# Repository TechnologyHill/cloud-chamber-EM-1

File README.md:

# Cloud Chamber EM-1

[more about cloud chamber](https://en.wikipedia.org/wiki/Cloud_chamber)

#### Our goal is make a small cloud chamber based on thermoelectric cooling.
#### viewport size is 100 mm x 200 mm.

")
")

## Cooling system

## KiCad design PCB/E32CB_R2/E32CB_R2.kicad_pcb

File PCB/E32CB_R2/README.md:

# ESP32 Control Board
**E32CB_R2**

KiCad render of PCB

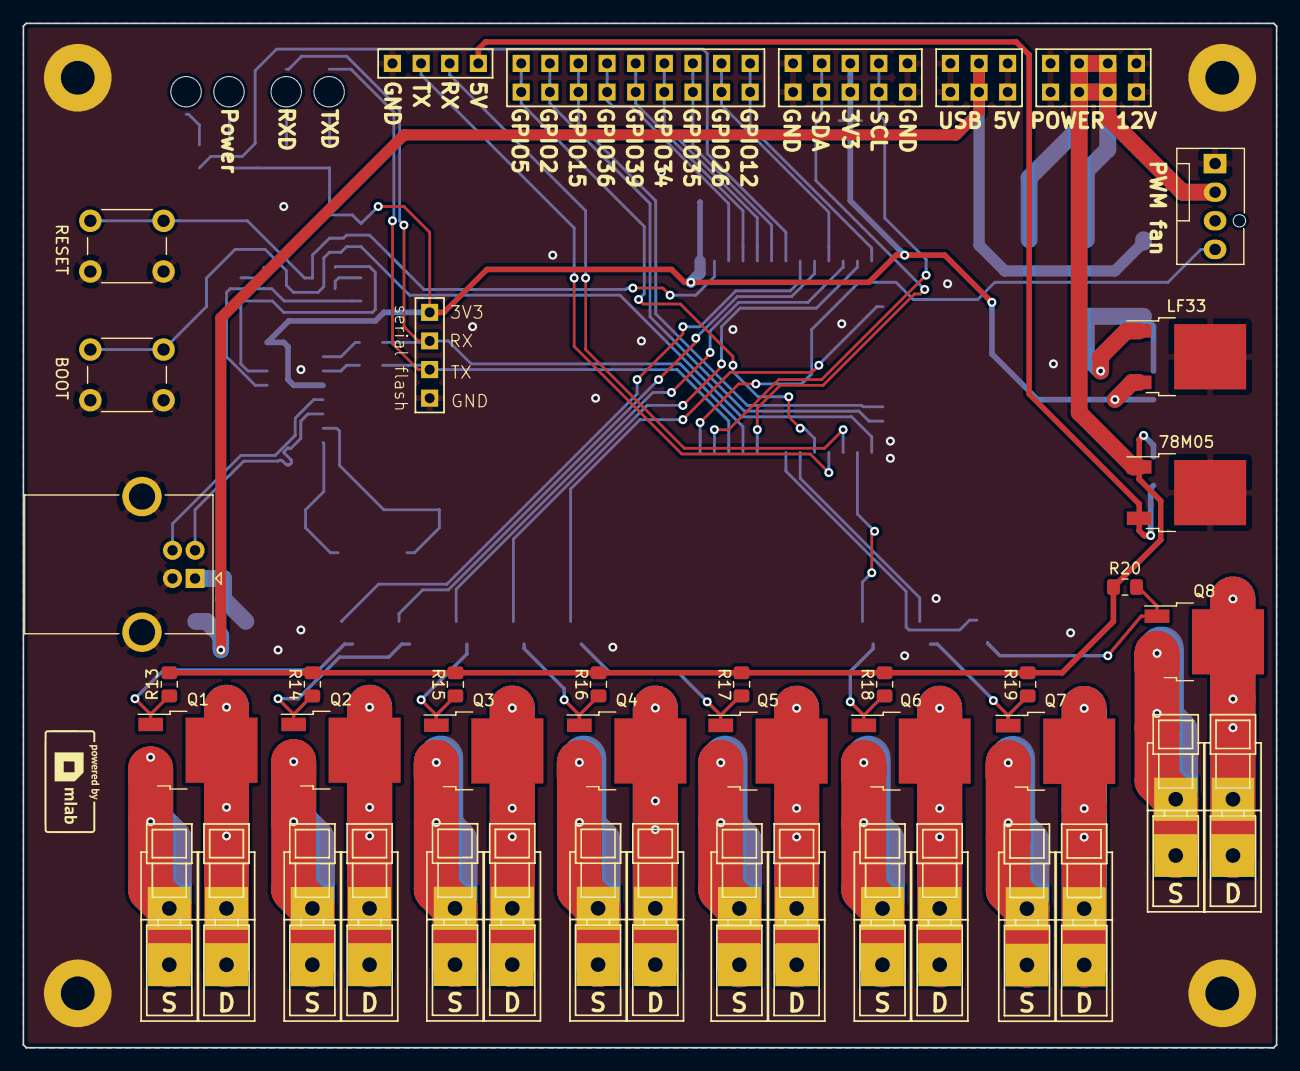
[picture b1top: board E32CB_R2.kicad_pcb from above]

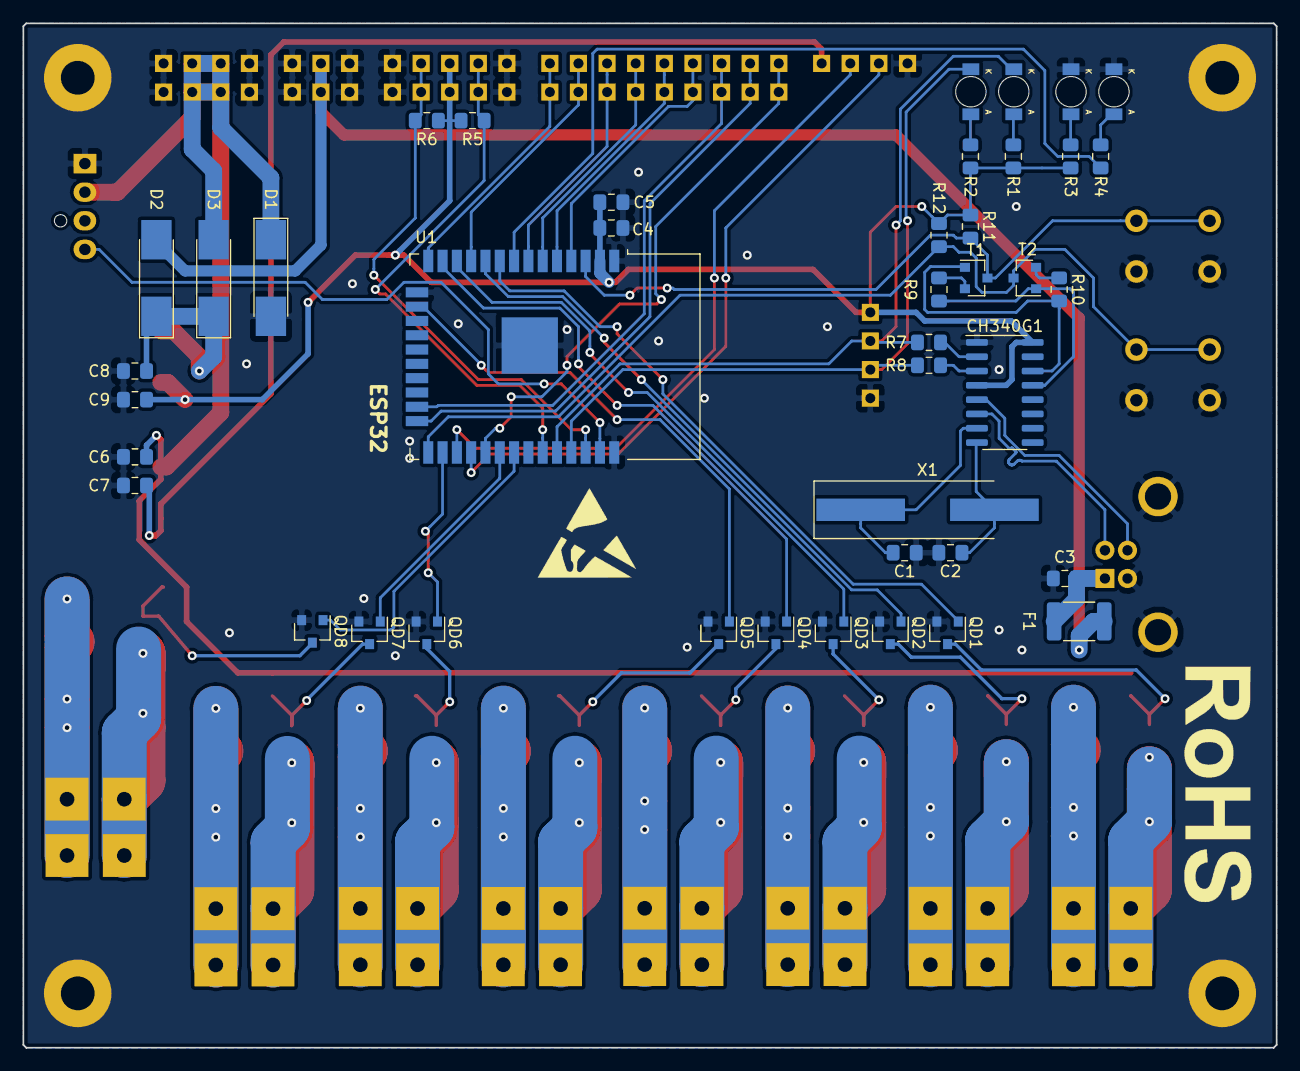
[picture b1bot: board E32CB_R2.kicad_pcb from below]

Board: 2 copper layers, 111.3 x 90.9 mm, 90 parts (42 on the bottom side), 72 nets.

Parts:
78M05: L7805; TO-252-2
BOOT: FLASH; SW_PUSH_6mm
C1, C2: 22p; C_0805_2012Metric_Pad1.15x1.40mm_HandSolder
C3: 10nF; C_0805_2012Metric_Pad1.15x1.40mm_HandSolder
C4, C7, C8: 100nF; C_0805_2012Metric_Pad1.15x1.40mm_HandSolder
C5: 10uF; C_0805_2012Metric_Pad1.15x1.40mm_HandSolder
C6: 330nF; C_0805_2012Metric_Pad1.15x1.40mm_HandSolder
C9: 2.2uF; C_0805_2012Metric_Pad1.15x1.40mm_HandSolder
CH340G1: CH340G; SOIC-16_3.9x9.9mm_P1.27mm
D: D; WAGO256
D1, D2, D3: 1N4007; D_MELF_Handsoldering
D#2, D#3, D#4, D#5, D#6, D#7, D#8: D; WAGO256
F1: 1A; Fuse_1812_4532Metric_Pad1.30x3.40mm_HandSolder
H1, H2, H3, H4: M3; MountingHole_3mm
J1: GPIO_HEADER; Straight_2x09
J2: Power; Straight_2x04
J3: USB_B; USB_B_OST_USB-B1HSxx_Horizontal
J4: USB +5V; Straight_2x03
J5: NEXTION; Straight_1x04
J6: I2C; Straight_2x05
J23: serial flash; Straight_1x04
LED1: RXD; LED_1206
LED2: TXD; LED_1206
LED3: Power; LED_1206
LED4: Signal; LED_1206
LF33: LF33_TO252; TO-252-2
PWM fan: Conn_01x04; FanPinHeader_1x04_P2.54mm_Vertical
Q1, Q2, Q3, Q4, Q5, Q6, Q7, Q8: IRLR8743; TO-252-2
QD1, QD2, QD3, QD4, QD5, QD6, QD7, QD8: BSS138; SOT-23
R1, R2, R3, R4: 1k; R_0805_2012Metric_Pad1.15x1.40mm_HandSolder
R5, R6: 1k2; R_0805_2012Metric_Pad1.15x1.40mm_HandSolder
R7, R8, R13, R14, R15, R16, R17, R18, R19, R20: 470R; R_0805_2012Metric_Pad1.15x1.40mm_HandSolder
R9, R10: 12k; R_0805_2012Metric_Pad1.15x1.40mm_HandSolder
R11, R12: 10k; R_0805_2012Metric_Pad1.15x1.40mm_HandSolder
RESET: RESET; SW_PUSH_6mm
S: S; WAGO256
S#2, S#3, S#4, S#5, S#6, S#7, S#8: S; WAGO256
T1, T2: S8050; SOT-23
U1: ESP32-WROOM-32
X1: 12MHz; Crystal_SMD_HC49-SD_HandSoldering

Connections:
+3V3: C4.1, C5.1, C9.1, CH340G1.4, CH340G1.16, J6.5, J6.6, J23.1, LF33.3, R1.2, R2.2, R3.2, R5.1, R6.1, R11.1, R12.1, U1.2
+5V: D2.2, F1.1, J4.3, J4.4
+12V: 78M05.1, C6.1, D1.1, D3.2, J2.3, J2.4, J2.5, J2.6, PWM fan.2, R13.1, R14.1, R15.1, R16.1, R17.1, R18.1, R19.1, R20.1
/EN: R11.2, RESET.1, T1.3, U1.3
/I2C_SCL: J6.7, J6.8, R6.2, U1.36
/I2C_SDA: J6.3, J6.4, R5.2, U1.33
/IO_0: BOOT.1, R12.2, T2.3, U1.25
/Q1: QD1.1, U1.9
/Q2: QD2.1, U1.10
/Q3: QD3.1, U1.12
/Q4: QD4.1, U1.13
/Q5: QD5.1, U1.16
/Q6: QD6.1, U1.26
/Q7: QD7.1, U1.30
/Q8: QD8.1, U1.31
/RXD: J23.2, LED1.1, R7.1, U1.34
/TXD: J23.3, LED2.1, R8.1, U1.35
/U2_RXD: J5.3, U1.27
/U2_TXD: J5.2, U1.28
/USB_N: CH340G1.6, J3.2
/USB_P: CH340G1.5, J3.3
/display_Vin: 78M05.3, C7.1, J5.4
/fan1: PWM fan.4, U1.37
/gpi34: J1.11, J1.12, U1.6
/gpi35: J1.13, J1.14, U1.7
/gpi36: J1.7, J1.8, U1.4
/gpi39: J1.9, J1.10, U1.5
/gpio2: J1.3, J1.4, U1.24
/gpio5: J1.1, J1.2, U1.29
/gpio12: J1.17, J1.18, U1.14
/gpio15: J1.5, J1.6, U1.23
/gpio26: J1.15, J1.16, U1.11
/s_LED: R4.2, U1.8
GND: 78M05.2, BOOT.2, C1.2, C2.2, C3.2, C4.2, C5.2, C6.2, C7.2, C8.2, C9.2, CH340G1.1, D1.2, H1.1, H2.1, H3.1, H4.1, J2.1, J2.2, J2.7, J2.8, J3.4, J3.5, J4.1, J4.2, J4.5, J4.6, J5.1, J6.1, J6.2, J6.9, J6.10, J23.4, LED3.1, LED4.1, LF33.2, PWM fan.1, QD1.2, QD2.2, QD3.2, QD4.2, QD5.2, QD6.2, QD7.2, QD8.2, RESET.2, U1.1, U1.15, U1.38, U1.39
unnamed: C8.1, D2.1, D3.1, LF33.1
unnamed: C1.1, CH340G1.7, X1.1
unnamed: C2.1, CH340G1.8, X1.2
unnamed: C3.1, F1.2, J3.1
unnamed: CH340G1.2, R7.2
unnamed: CH340G1.3, R8.2
unnamed: CH340G1.13, R9.2, T2.1
unnamed: CH340G1.14, R10.2, T1.1
unnamed: D#7.1, Q1.2
unnamed: Q1.3, S#7.1
unnamed: D#8.1, Q2.2
unnamed: Q2.3, S#8.1
unnamed: D.1, Q3.2
unnamed: Q3.3, S#2.1
unnamed: D#2.1, Q4.2
unnamed: Q4.3, S.1
unnamed: D#6.1, Q7.2
unnamed: Q7.3, S#3.1
unnamed: D#3.1, Q8.2
unnamed: Q8.3, S#4.1
unnamed: D#4.1, Q5.2
unnamed: Q5.3, S#6.1
unnamed: D#5.1, Q6.2
unnamed: Q6.3, S#5.1
unnamed: LED1.2, R1.1
unnamed: LED2.2, R2.1
unnamed: LED3.2, R3.1
unnamed: LED4.2, R4.1
unnamed: Q1.1, QD1.3, R13.2
unnamed: Q2.1, QD2.3, R14.2
unnamed: Q3.1, QD3.3, R15.2
unnamed: Q4.1, QD4.3, R16.2
unnamed: Q5.1, QD5.3, R17.2
unnamed: Q6.1, QD6.3, R18.2
unnamed: Q7.1, QD7.3, R19.2
unnamed: Q8.1, QD8.3, R20.2
unnamed: R9.1, T1.2
unnamed: R10.1, T2.2

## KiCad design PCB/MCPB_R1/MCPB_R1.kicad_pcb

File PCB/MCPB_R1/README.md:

# MCP9808 Board
**MCPB_R1**

top view of PCB

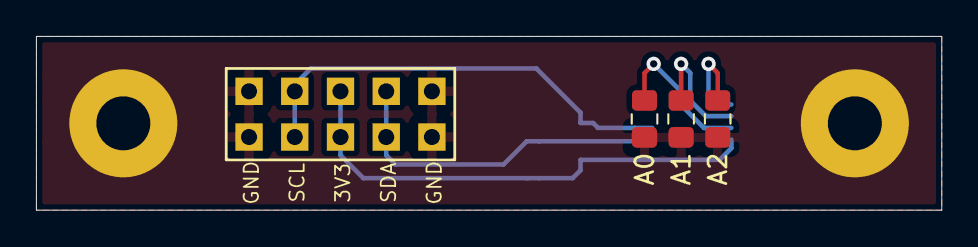
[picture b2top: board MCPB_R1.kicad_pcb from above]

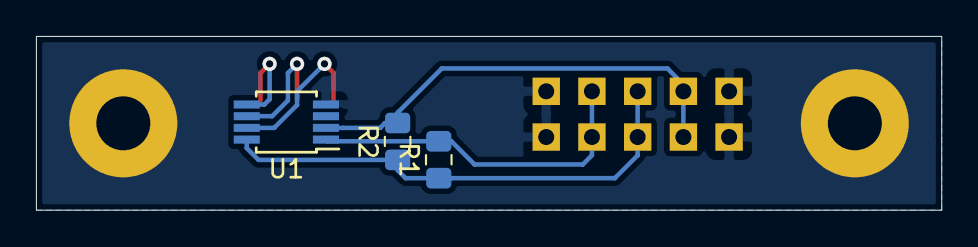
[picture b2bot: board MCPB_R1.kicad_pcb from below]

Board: 2 copper layers, 50.3 x 9.7 mm, 9 parts (3 on the bottom side), 7 nets.

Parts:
A0, A1, A2: HEADER_2x01; R_0805_2012Metric_Pad1.15x1.40mm_HandSolder
J1: HEADER_2x05_PARALLEL; Straight_2x05
M1, M2: HOLE; MountingHole_3mm
R1, R2: 4k7; R_0805_2012Metric_Pad1.15x1.40mm_HandSolder
U1: MCP9804_MSOP; MSOP-8_3x3mm_P0.65mm

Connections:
+3V3: J1.5, J1.6, R1.1, R2.1, U1.8
/scl: J1.3, J1.4, R2.2, U1.2
/sda: J1.7, J1.8, R1.2, U1.1
GND: A0.1, A1.1, A2.1, J1.1, J1.2, J1.9, J1.10, M1.1, M2.1, U1.4
unnamed: A0.2, U1.7
unnamed: A1.2, U1.6
unnamed: A2.2, U1.5

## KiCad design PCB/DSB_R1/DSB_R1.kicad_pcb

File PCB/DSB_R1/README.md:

# DS18B20 Board
**DSB_R1**

top view of PCB

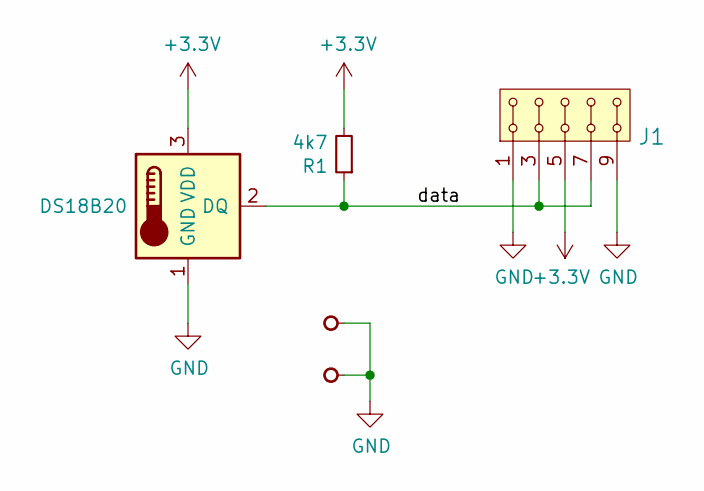
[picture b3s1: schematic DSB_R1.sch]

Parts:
J1: HEADER_2x05_PARALLEL; Straight_2x05
M1, M2: HOLE; MountingHole_3mm
R1: 4k7; R_0805_2012Metric_Pad1.15x1.40mm_HandSolder
U1: DS18B20; TO-92_Inline

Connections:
+3V3: J1.5, J1.6, R1.2, U1.3 (VDD)
/data: J1.3, J1.4, J1.7, J1.8, R1.1, U1.2 (DQ)
GND: J1.1, J1.2, J1.9, J1.10, M1.1, M2.1, U1.1 (GND)

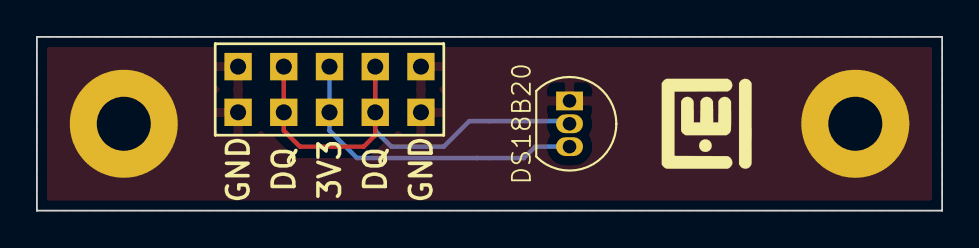
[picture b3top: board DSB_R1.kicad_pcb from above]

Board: 2 copper layers, 50.3 x 9.7 mm, 5 parts (1 on the bottom side), 3 nets.

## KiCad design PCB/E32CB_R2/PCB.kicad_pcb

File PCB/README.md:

**All PCBs are created in KiCad**

This PCBs are compatible with [MLAB](https://github.com/MLAB-project/Modules).

We use [MLAB footprints](https://github.com/MLAB-project/kicad-mlab).

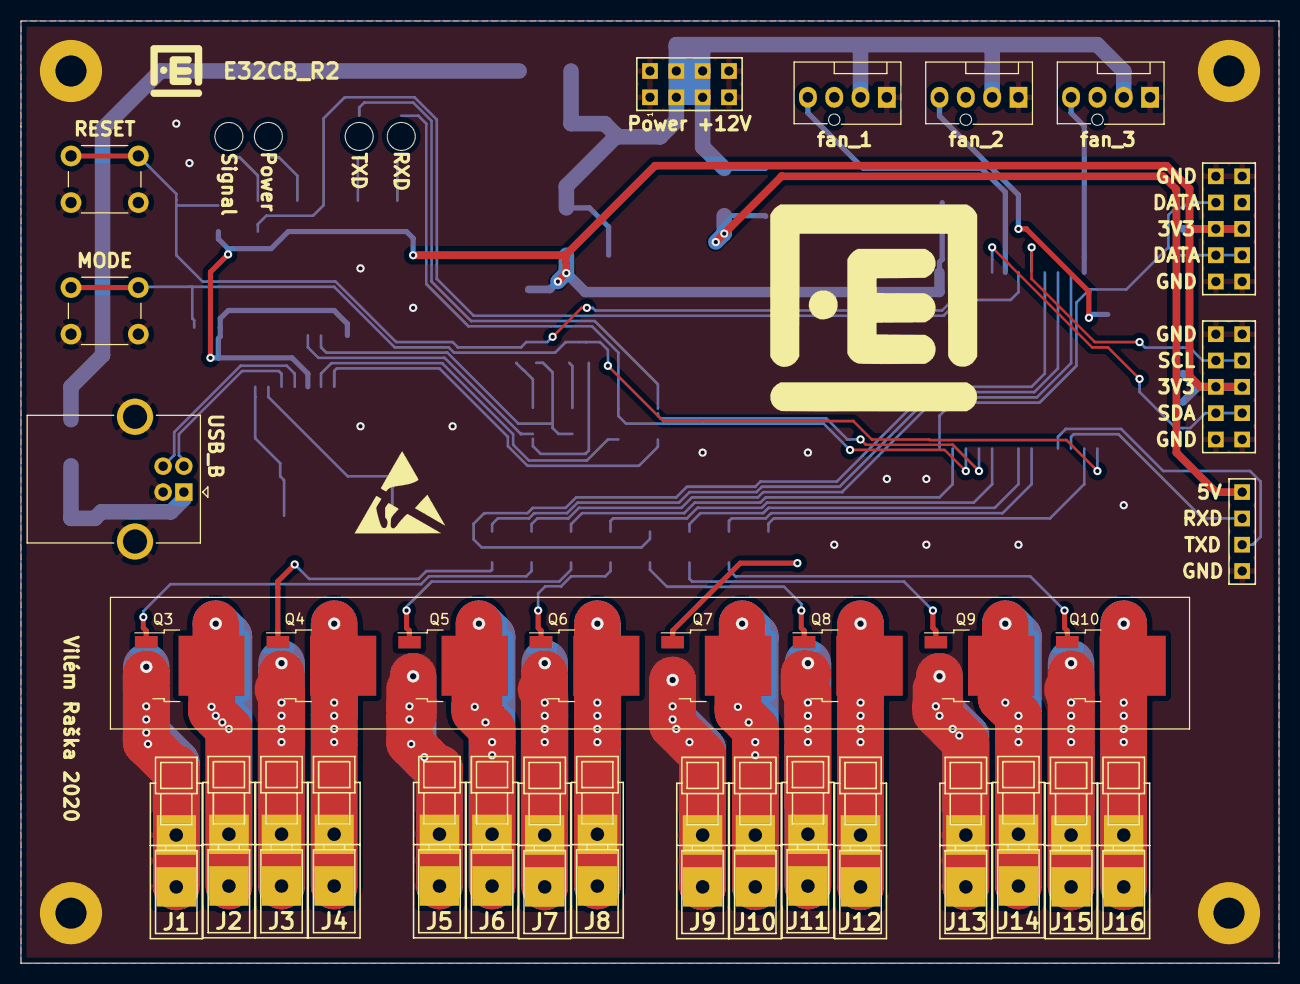
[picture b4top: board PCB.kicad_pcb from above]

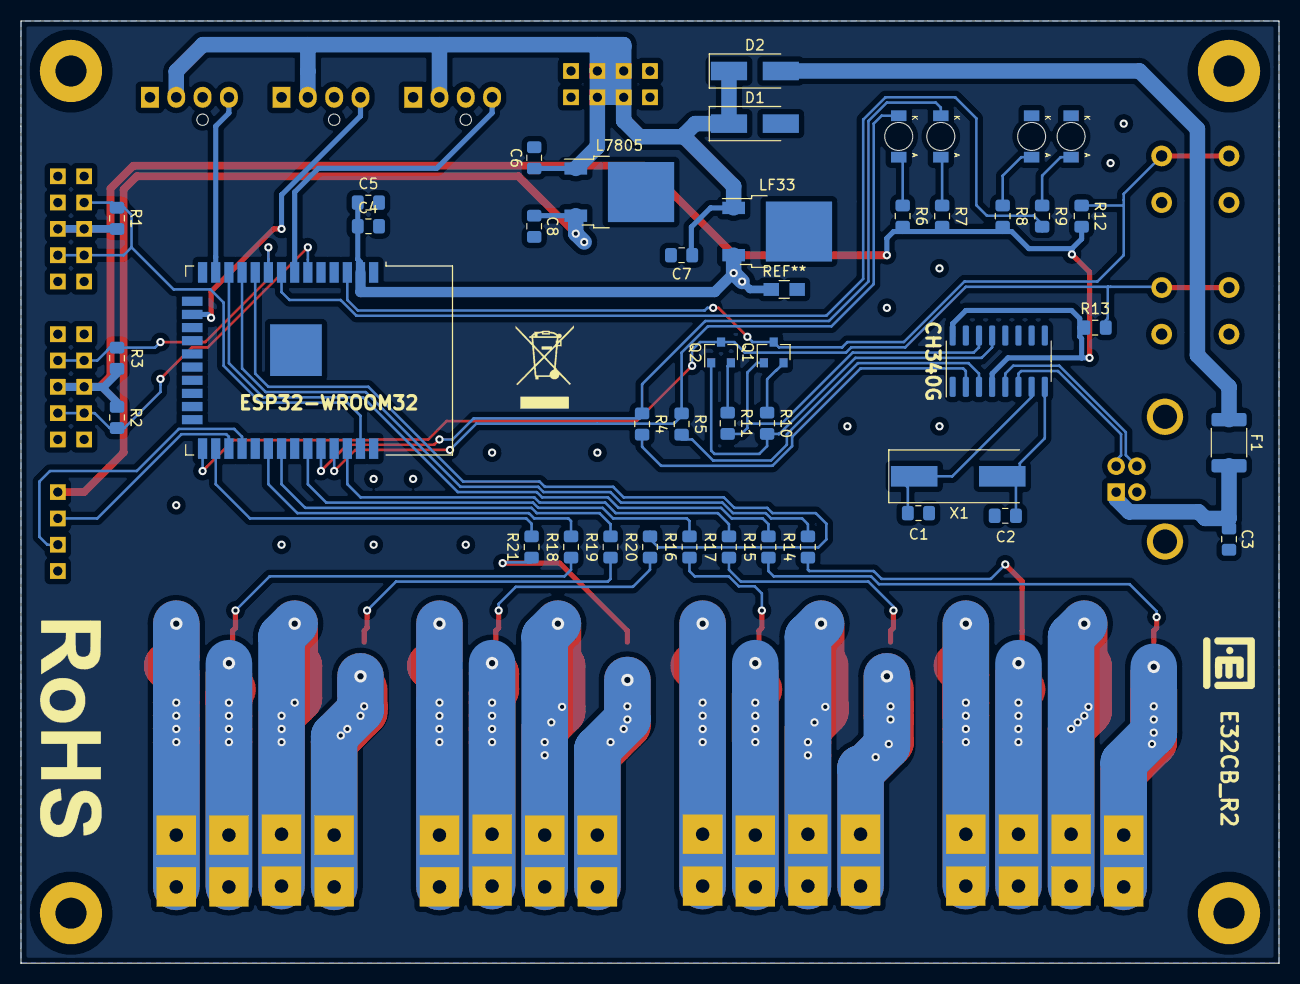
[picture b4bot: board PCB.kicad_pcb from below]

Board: 2 copper layers, 121.4 x 90.9 mm, 81 parts (43 on the bottom side), 57 nets.

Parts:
C1, C2: 22p; C_0805_2012Metric_Pad1.15x1.40mm_HandSolder
C3: 10nF; C_0805_2012Metric_Pad1.15x1.40mm_HandSolder
C4, C7, C8: 100nF; C_0805_2012Metric_Pad1.15x1.40mm_HandSolder
C5: 10uF; C_0805_2012Metric_Pad1.15x1.40mm_HandSolder
C6: 330nF; C_0805_2012Metric_Pad1.15x1.40mm_HandSolder
CH340G: CH340G; SOIC-16_3.9x9.9mm_P1.27mm
D1, D2: 1N4007; D_SMA_Handsoldering
ESP32-WROOM32: ESP32-WROOM-32
F1: 1A; Fuse_1812_4532Metric_Pad1.30x3.40mm_HandSolder
H1, H2, H3, H4: M3; MountingHole_3mm
J1, J3, J5, J7, J9, J11, J13, J15: GND; WAGO256
J2: pump; WAGO256
J4: LED; WAGO256
J6: P12B; WAGO256
J8: P12A; WAGO256
J10: VM1; WAGO256
J12: VM2; WAGO256
J14: P3B; WAGO256
J16: P3A; WAGO256
J17: NEXTION; Straight_1x04
J18: Power; Straight_2x04
J19: OneWire; Straight_2x05
J20: I2C; Straight_2x05
L7805: 5Vstabilizer; TO-252-2
LF33: 3V3stabilizer; TO-252-2
MODE: SW_Push; SW_PUSH_6mm_h4.3mm
Power: LED_R; LED_1206
Q1, Q2: S8050; SOT-23
Q3, Q4, Q5, Q6, Q7, Q8, Q9, Q10: IRLR2905; TO-252-2
R1: 4k7; R_0805_2012Metric_Pad1.15x1.40mm_HandSolder
R2, R3: 1k2; R_0805_2012Metric_Pad1.15x1.40mm_HandSolder
R4, R5, R14, R15, R16, R17, R18, R19, R20, R21: 470R; R_0805_2012Metric_Pad1.15x1.40mm_HandSolder
R6, R7, R8, R9: 1k; R_0805_2012Metric_Pad1.15x1.40mm_HandSolder
R10, R11: 12k; R_0805_2012Metric_Pad1.15x1.40mm_HandSolder
R12, R13: 10k; R_0805_2012Metric_Pad1.15x1.40mm_HandSolder
RESET: SW_Push; SW_PUSH_6mm_h4.3mm
RXD: LED_R; LED_1206
Signal: LED_R; LED_1206
TXD: LED_R; LED_1206
USB_B: USB_B; USB_B_OST_USB-B1HSxx_Horizontal
X1: 12MHz; Crystal_SMD_HC49-SD
fan_1, fan_2, fan_3: Conn_01x04; FanPinHeader_1x04_P2.54mm_Vertical

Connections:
+3V3: C4.1, C5.1, CH340G.4, CH340G.16, ESP32-WROOM32.2, J19.5, J19.6, J20.5, J20.6, LF33.3, R1.2, R2.1, R3.1, R6.2, R7.2, R8.2, R12.1, R13.1
+5V: D2.2, F1.1
+12V: C6.1, C7.1, D1.1, D2.1, J18.3, J18.4, J18.5, J18.6, L7805.1, LF33.1, fan_1.2, fan_2.2, fan_3.2
/EN: ESP32-WROOM32.3, Q1.3, R12.2, RESET.1
/I2C_SCL: ESP32-WROOM32.9, J20.7, J20.8, R3.2
/I2C_SDA: ESP32-WROOM32.6, J20.3, J20.4, R2.2
/IO_0: ESP32-WROOM32.25, MODE.1, Q2.3, R13.2
/LED: ESP32-WROOM32.11, R14.2
/OneWire: ESP32-WROOM32.37, J19.3, J19.4, J19.7, J19.8, R1.1
/P3A: ESP32-WROOM32.30, R18.2
/P3B: ESP32-WROOM32.31, R19.2
/P12A: ESP32-WROOM32.33, R16.2
/P12B: ESP32-WROOM32.36, R17.2
/RXD: ESP32-WROOM32.35, R5.1, RXD.1
/TXD: ESP32-WROOM32.34, R4.1, TXD.1
/U2_RXD: ESP32-WROOM32.27, J17.3
/U2_TXD: ESP32-WROOM32.28, J17.2
/USB_N: CH340G.6, USB_B.2
/USB_P: CH340G.5, USB_B.3
/VM1: ESP32-WROOM32.26, R21.2
/VM2: ESP32-WROOM32.10, R20.2
/display_Vin: C8.1, J17.4, L7805.3
/fan1: ESP32-WROOM32.7, fan_1.4
/fan2: ESP32-WROOM32.16, fan_2.4
/fan3: ESP32-WROOM32.13, fan_3.4
/pump: ESP32-WROOM32.12, R15.2
/s_LED: ESP32-WROOM32.8, R9.2
GND: C1.2, C2.2, C3.2, C4.2, C5.2, C6.2, C7.2, C8.2, CH340G.1, D1.2, ESP32-WROOM32.1, ESP32-WROOM32.15, ESP32-WROOM32.38, H1.1, H2.1, H3.1, H4.1, J1.1, J3.1, J5.1, J7.1, J9.1, J11.1, J13.1, J15.1, J17.1, J18.1, J18.2, J18.7, J18.8, J19.1, J19.2, J19.9, J19.10, J20.1, J20.2, J20.9, J20.10, L7805.2, LF33.2, MODE.2, Power.1, Q3.3, Q4.3, Q5.3, Q6.3, Q7.3, Q8.3, Q9.3, Q10.3, RESET.2, Signal.1, USB_B.4, USB_B.5, fan_1.1, fan_2.1, fan_3.1
unnamed: C1.1, CH340G.7, X1.1
unnamed: C2.1, CH340G.8, X1.2
unnamed: C3.1, F1.2, USB_B.1
unnamed: CH340G.2, R4.2
unnamed: CH340G.3, R5.2
unnamed: CH340G.13, Q2.1, R10.2
unnamed: CH340G.14, Q1.1, R11.2
unnamed: J2.1, Q3.2
unnamed: J4.1, Q4.2
unnamed: J6.1, Q5.2
unnamed: J8.1, Q6.2
unnamed: J10.1, Q7.2
unnamed: J12.1, Q8.2
unnamed: J14.1, Q9.2
unnamed: J16.1, Q10.2
unnamed: Power.2, R8.1
unnamed: Q1.2, R10.1
unnamed: Q2.2, R11.1
unnamed: Q3.1, R15.1
unnamed: Q4.1, R14.1
unnamed: Q5.1, R17.1
unnamed: Q6.1, R16.1
unnamed: Q7.1, R21.1
unnamed: Q8.1, R20.1
unnamed: Q9.1, R19.1
unnamed: Q10.1, R18.1
unnamed: R6.1, RXD.2
unnamed: R7.1, TXD.2
unnamed: R9.1, Signal.2

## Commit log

2019-06-03 L_2015_profile
2019-06-04 L_profile
2019-06-04 T_profile
2019-06-06 L_profile fixed
2019-06-12 screws parameters
2019-06-27 rendering images
2019-06-27 Cooling schema
2019-06-27 readme
2019-07-01 readme update
2019-07-01 fix readme
2019-07-06 added makefile
2019-07-30 schema added
2019-07-31 makefile updated
2019-08-12 makefile, parameters and readme
2019-08-12 schema update
2019-08-12 fix schema
2019-08-28 footprint update
2019-08-29 1001_AB.scad added
2019-08-30 uprava PCB
2019-08-30 1001_AB update
2019-08-30 rendering models
2019-08-30 1001_AB upgrade
2019-08-31 rename 1001_Pbk
2019-09-03 pcb modified
2019-09-04 PCB update
2019-09-05 models rendering and 2001_Pbk
2019-09-06 new readme #2
2019-09-06 readme update #2
2019-09-06 parameters update
2019-09-07 PCB readme update
2019-09-08 pin fix
2019-09-09 oprava hozměrů nextionu #3
2019-09-09 pcb update #4
2019-09-10 pdf created #4
2019-09-11 software
2019-09-12 Create LICENSE
2019-09-12 nextion library created
2019-09-14 PCB reated #4
2019-09-15 gerbers created
2019-09-15 readme update #4
2019-09-16 alu profile added
2019-09-18 PCB General UPGRADE
2019-09-18 PCB silkscreen update
2019-09-19 new alu profiles library
2019-09-23 chamber main frame added
2019-09-23 ALU profile R - radius update
2019-09-23 part rename
2019-09-23 new library for NEXTION #5
2019-09-24 frame update
2019-09-24 fix picture in readme
2019-09-28 ALU profile name fixed
2019-09-28 added .gitgnore
2019-09-29 Cu deska
2019-10-07 Cu block fixed
2019-11-12 readme #4
2019-11-12 CAD readme
2019-11-30 schema deleted
2019-11-30 module nextion
2019-12-02 pcb readme
2019-12-09 pcb, power and 3v3
2019-12-10 pwm fan #4
2019-12-10 pcb mounting holes #4
2019-12-10 PWM cooling fans #4
2019-12-10 I2C #4
2019-12-10 NEXTION connector #4
2019-12-10 blocks align #4
2019-12-10 OneWire #4
2019-12-10 schema #4
2019-12-10 pcb dir update
2019-12-10 footprint update #4
2019-12-11 OneWire update #4
2019-12-11 pump added
2019-12-11 USB CH340G update #4
2019-12-11 LED indicator #4
2019-12-11 schema update #4
2019-12-16 fan & radiator
2019-12-16 renderig models (fan)
2019-12-16 radiator assembly
2019-12-16 renderig models
2019-12-17 3101 rendering
2019-12-17 unit conversions
2019-12-17 radiator
2019-12-17 makefile
2019-12-17 fitting
2019-12-17 fan upgrade
2019-12-17 radiator and fan
2019-12-18 reset circuit update
2019-12-18 pdf schema update
2019-12-18 logo added #4
2019-12-18 bad logo
2019-12-18 mosfet added #4
2019-12-18 peltiers #4
2019-12-19 MOSFET gate R added #4
2019-12-19 PDF schema update #4
2019-12-19 LED + pump #4
2019-12-19 schema restructure #4
2019-12-19 mlab schematics added #4
2019-12-20 pdf update #4
2019-12-21 pcb #4
2019-12-30 fitting dimensions update
2019-12-30 fitting dimensions upgrade
2019-12-30 pump dimensions update
2019-12-30 fan dimensions update
2019-12-30 radiator dimensions update
2019-12-30 3101 update
2019-12-30 rendering components
2019-12-30 3101 upgrade
2019-12-30 alu frame update
2020-01-02 logo added
2020-01-02 silkscreen logo added
2020-01-03 colored logo
2020-01-03 logo color update
2020-01-03 color readme
2020-01-03 colors update
2020-01-04 pcb dimensions and mounting holes #4
2020-01-04 components added into board #4
2020-01-04 reset circuit #4
2020-01-04 indication LED #4
2020-01-04 pcb finish #4
2020-01-05 gerber #4
2020-01-05 gerber regenerate
2020-01-06 sw path update
2020-01-06 CDA path update
2020-01-06 new render of cloud chamber
2020-01-06 del old files
2020-01-06 better render of cloud chamber
2020-01-07 render image move
2020-01-07 chamber update
2020-01-07 modules position
2020-01-08 ESP files added
2020-01-08 E32CB_R2 path update
2020-01-08 1206 to 0805
2020-01-09 rendering stl
2020-01-09 DSB_R1 created
2020-01-09 rename and update
2020-01-10 diferential pair length
2020-01-10 gerber zip
2020-01-10 gerber, powered by mlab
2020-01-13 conflict fixed
2020-01-14 MCPB_R1 update
2020-01-14 E32CB_RB update
2020-02-01 logo update
2020-02-01 circle logo silkscreen
2020-02-09 pcb render added
2020-02-09 gerber added
2020-02-09 readme and folder update
2020-02-09 gitignore update
2020-02-09 fp-lib-table deleted
2020-02-15 logger
2020-02-15 time added to log
2020-02-15 good output
2020-02-15 counting temperature sensors
2020-02-16 generated charts
2020-02-16 chart added to md
2020-02-16 data log update
2020-02-17 code optimalization
2020-02-17 flags and help added to logger
2020-02-17 final release 1.0
2020-02-17 pcb schema update
2020-02-17 pdf schema
2020-02-17 USB voltage distribution
2020-02-17 image render
2020-02-17 gerber generated
2020-02-17 DSB_R1 md update
2020-02-17 MCPB_R1 image update
2020-03-03 esp pin update, pin header added
2020-03-21 NopSCADlib added
2020-03-21 NopSCADlib added as submodule
2020-04-17 pcb delete
2020-04-17 module size
2020-04-17 mosfets position
2020-04-17 reset section
2020-04-18 components on board
2020-04-18 stabilizers position
2020-04-18 diodes connection
2020-04-18 3v3 update
2020-04-18 gpio neprohozeny
2020-04-18 gpio header pins changed
2020-04-18 pdf exported
2020-04-19 gpio chenged
2020-04-19 pdf schema exported
2020-04-19 gpio connected
2020-04-19 mosfet connection
2020-04-19 conection finished
2020-04-19 all conection finished
2020-04-19 filled zones
2020-04-19 vias added
2020-04-19 silk screen update
2020-04-19 pcb images rendered
2020-04-20 track update
2020-04-20 refill zones
2020-04-20 silscreen update
2020-04-20 images render
2020-04-28 gerber exported
2020-04-28 pdf to gerber
2020-04-28 powered by mlab added
2020-07-14 MOSFET driving
2020-07-14 PCB refresh
2020-07-15 serial flash added
2020-07-15 schematic finished
2020-07-15 wago layout finished
2020-07-15 wago position on PCB finished
2020-07-15 all conponents placed on PCB
2020-07-15 GPIO header connected
2020-07-15 gate pullup added
2020-07-16 PCB connections finished
2020-07-16 filled PCB
2020-07-16 images update
2020-07-16 regenerate gerber
2020-07-16 MCPB update
2020-07-16 temperature sensor fixed
2020-07-17 final documentation to E32CB
2020-07-18 F.Silk update
2020-07-18 images rendered
2020-07-21 gerber for stencil generated
2020-07-22 gerber for stencil
2020-09-05 python2 to python3 update
2020-09-05 v1.1
2020-10-20 schematics update
2021-07-01 PCBs separated from repository
